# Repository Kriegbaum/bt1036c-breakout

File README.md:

# bt1036c-breakout
Breakout board for Feasy bt1036c bluetooth audio module

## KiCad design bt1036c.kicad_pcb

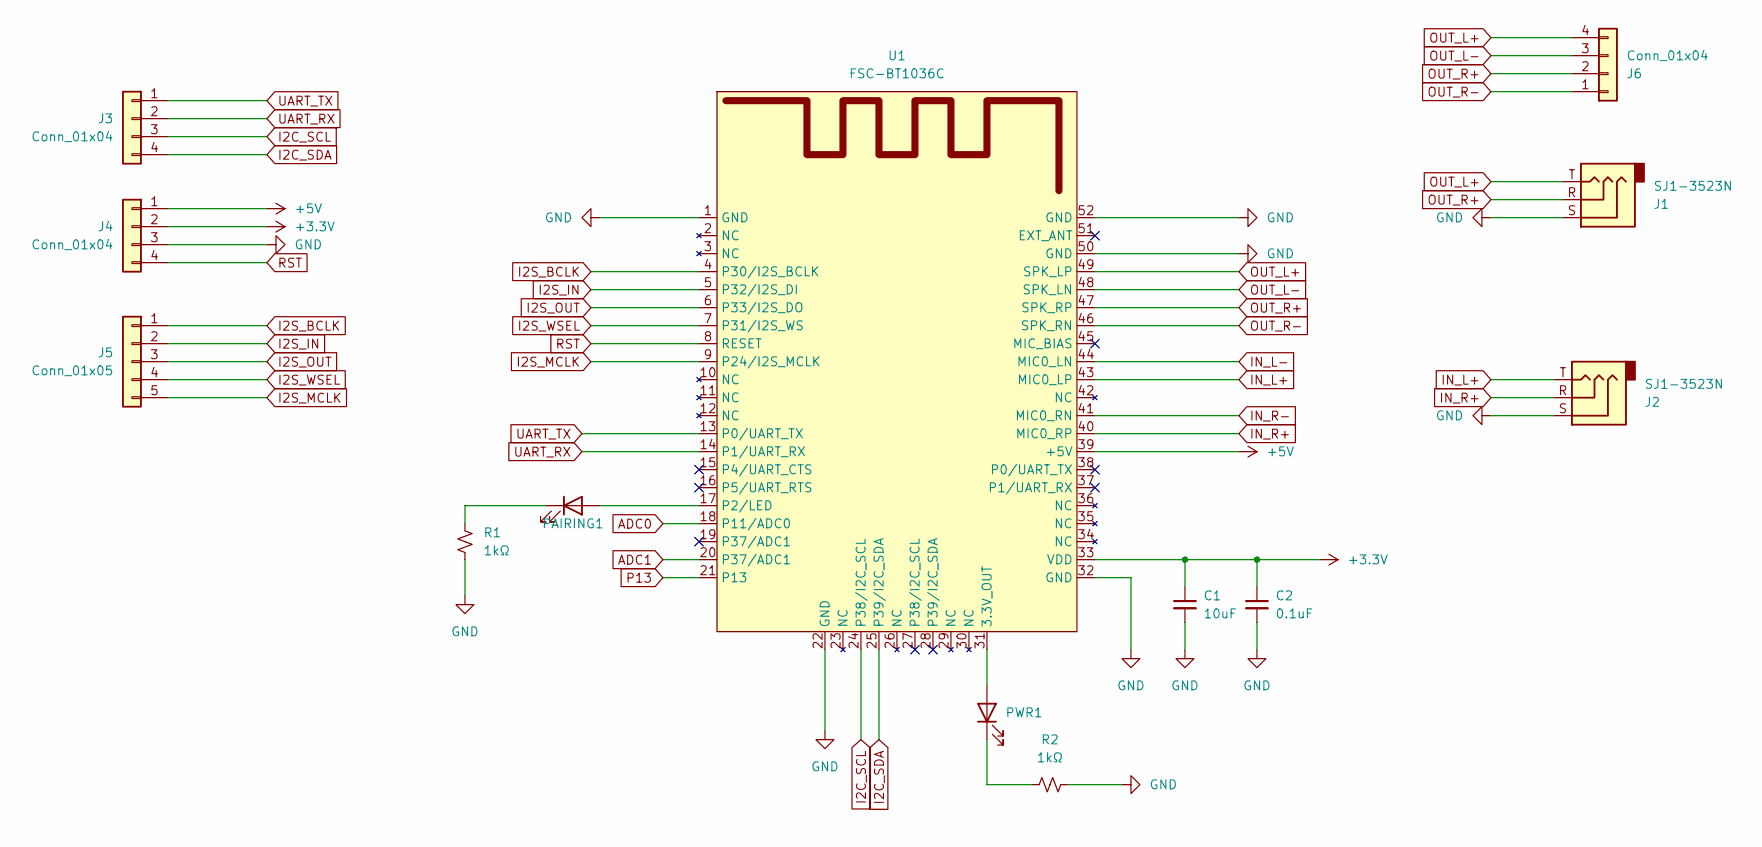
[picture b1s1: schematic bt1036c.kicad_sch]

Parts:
C1: CL21A106KOQNNNE; 0805_cap; Tolerance 20%; Voltage 16v
C2: CL21B104KBCNNNC; 0805_cap; Tolerance 10%; Voltage 50v
J1, J2: SJ1-3523N; Jack_3.5mm_CUI_SJ1-3523N_Horizontal
J3, J4, J6: Conn_01x04; PinHeader_1x04_P2.54mm_Vertical
J5: Conn_01x05; PinHeader_1x05_P2.54mm_Vertical
PAIRING1: QBLP615-IB; LED_1206_3216Metric_Pad1.42x1.75mm_HandSolder
PWR1: QBLP615-R; LED_1206_3216Metric_Pad1.42x1.75mm_HandSolder
R1, R2: RNCP0805FTD1K00; R_0805_2012Metric_Pad1.20x1.40mm_HandSolder
U1: FSC-BT1036C; fsc-bt1036c

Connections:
+3.3V: C1.1, C2.1, J4.2, U1.33 (VDD)
+5V: J4.1, U1.39 (+5V)
ADC0: U1.18 (P11/ADC0)
ADC1: U1.20 (P37/ADC1)
GND: C1.2, C2.2, J1.S, J2.S, J4.3, R1.1, R2.2, U1.1 (GND), U1.22 (GND), U1.32 (GND), U1.50 (GND), U1.52 (GND)
I2C_SCL: J3.3, U1.24 (P38/I2C_SCL)
I2C_SDA: J3.4, U1.25 (P39/I2C_SDA)
I2S_BCLK: J5.1, U1.4 (P30/I2S_BCLK)
I2S_IN: J5.2, U1.5 (P32/I2S_DI)
I2S_MCLK: J5.5, U1.9 (P24/I2S_MCLK)
I2S_OUT: J5.3, U1.6 (P33/I2S_DO)
I2S_WSEL: J5.4, U1.7 (P31/I2S_WS)
IN_L+: J2.T, U1.43 (MIC0_LP)
IN_L-: U1.44 (MIC0_LN)
IN_R+: J2.R, U1.40 (MIC0_RP)
IN_R-: U1.41 (MIC0_RN)
unnamed: PAIRING1.2 (A), U1.17 (P2/LED)
unnamed: PAIRING1.1 (K), R1.2
unnamed: PWR1.2 (A), U1.31 (3.3V_OUT)
unnamed: PWR1.1 (K), R2.1
OUT_L+: J1.T, J6.4, U1.49 (SPK_LP)
OUT_L-: J6.3, U1.48 (SPK_LN)
OUT_R+: J1.R, J6.2, U1.47 (SPK_RP)
OUT_R-: J6.1, U1.46 (SPK_RN)
P13: U1.21 (P13)
RST: J4.4, U1.8 (RESET)
UART_RX: J3.2, U1.14 (P1/UART_RX)
UART_TX: J3.1, U1.13 (P0/UART_TX)

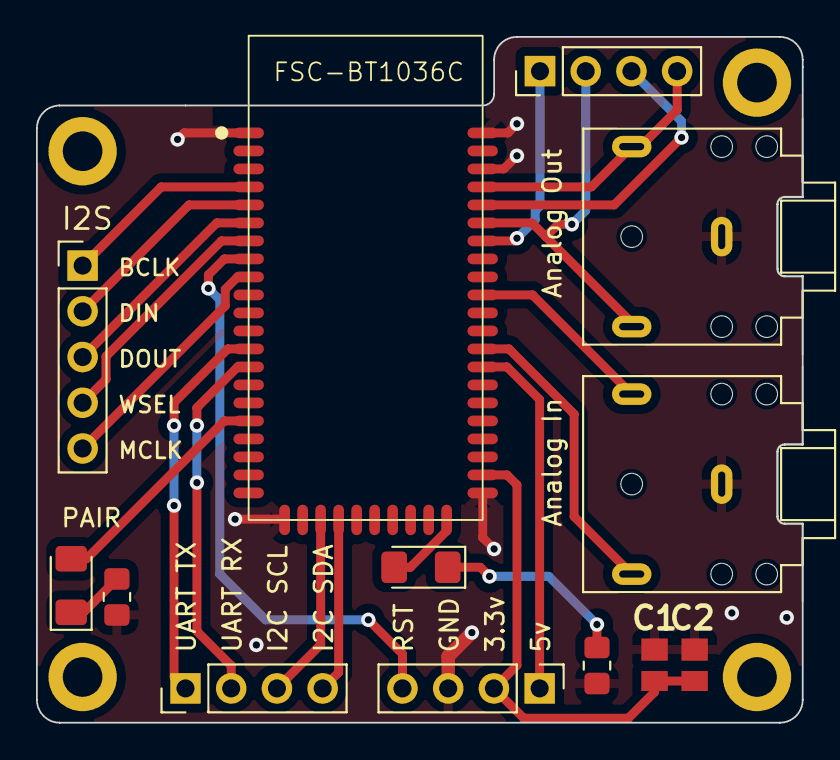
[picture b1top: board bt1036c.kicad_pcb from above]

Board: 2 copper layers, 42.5 x 38.1 mm, 13 parts (0 on the bottom side), 23 nets.
